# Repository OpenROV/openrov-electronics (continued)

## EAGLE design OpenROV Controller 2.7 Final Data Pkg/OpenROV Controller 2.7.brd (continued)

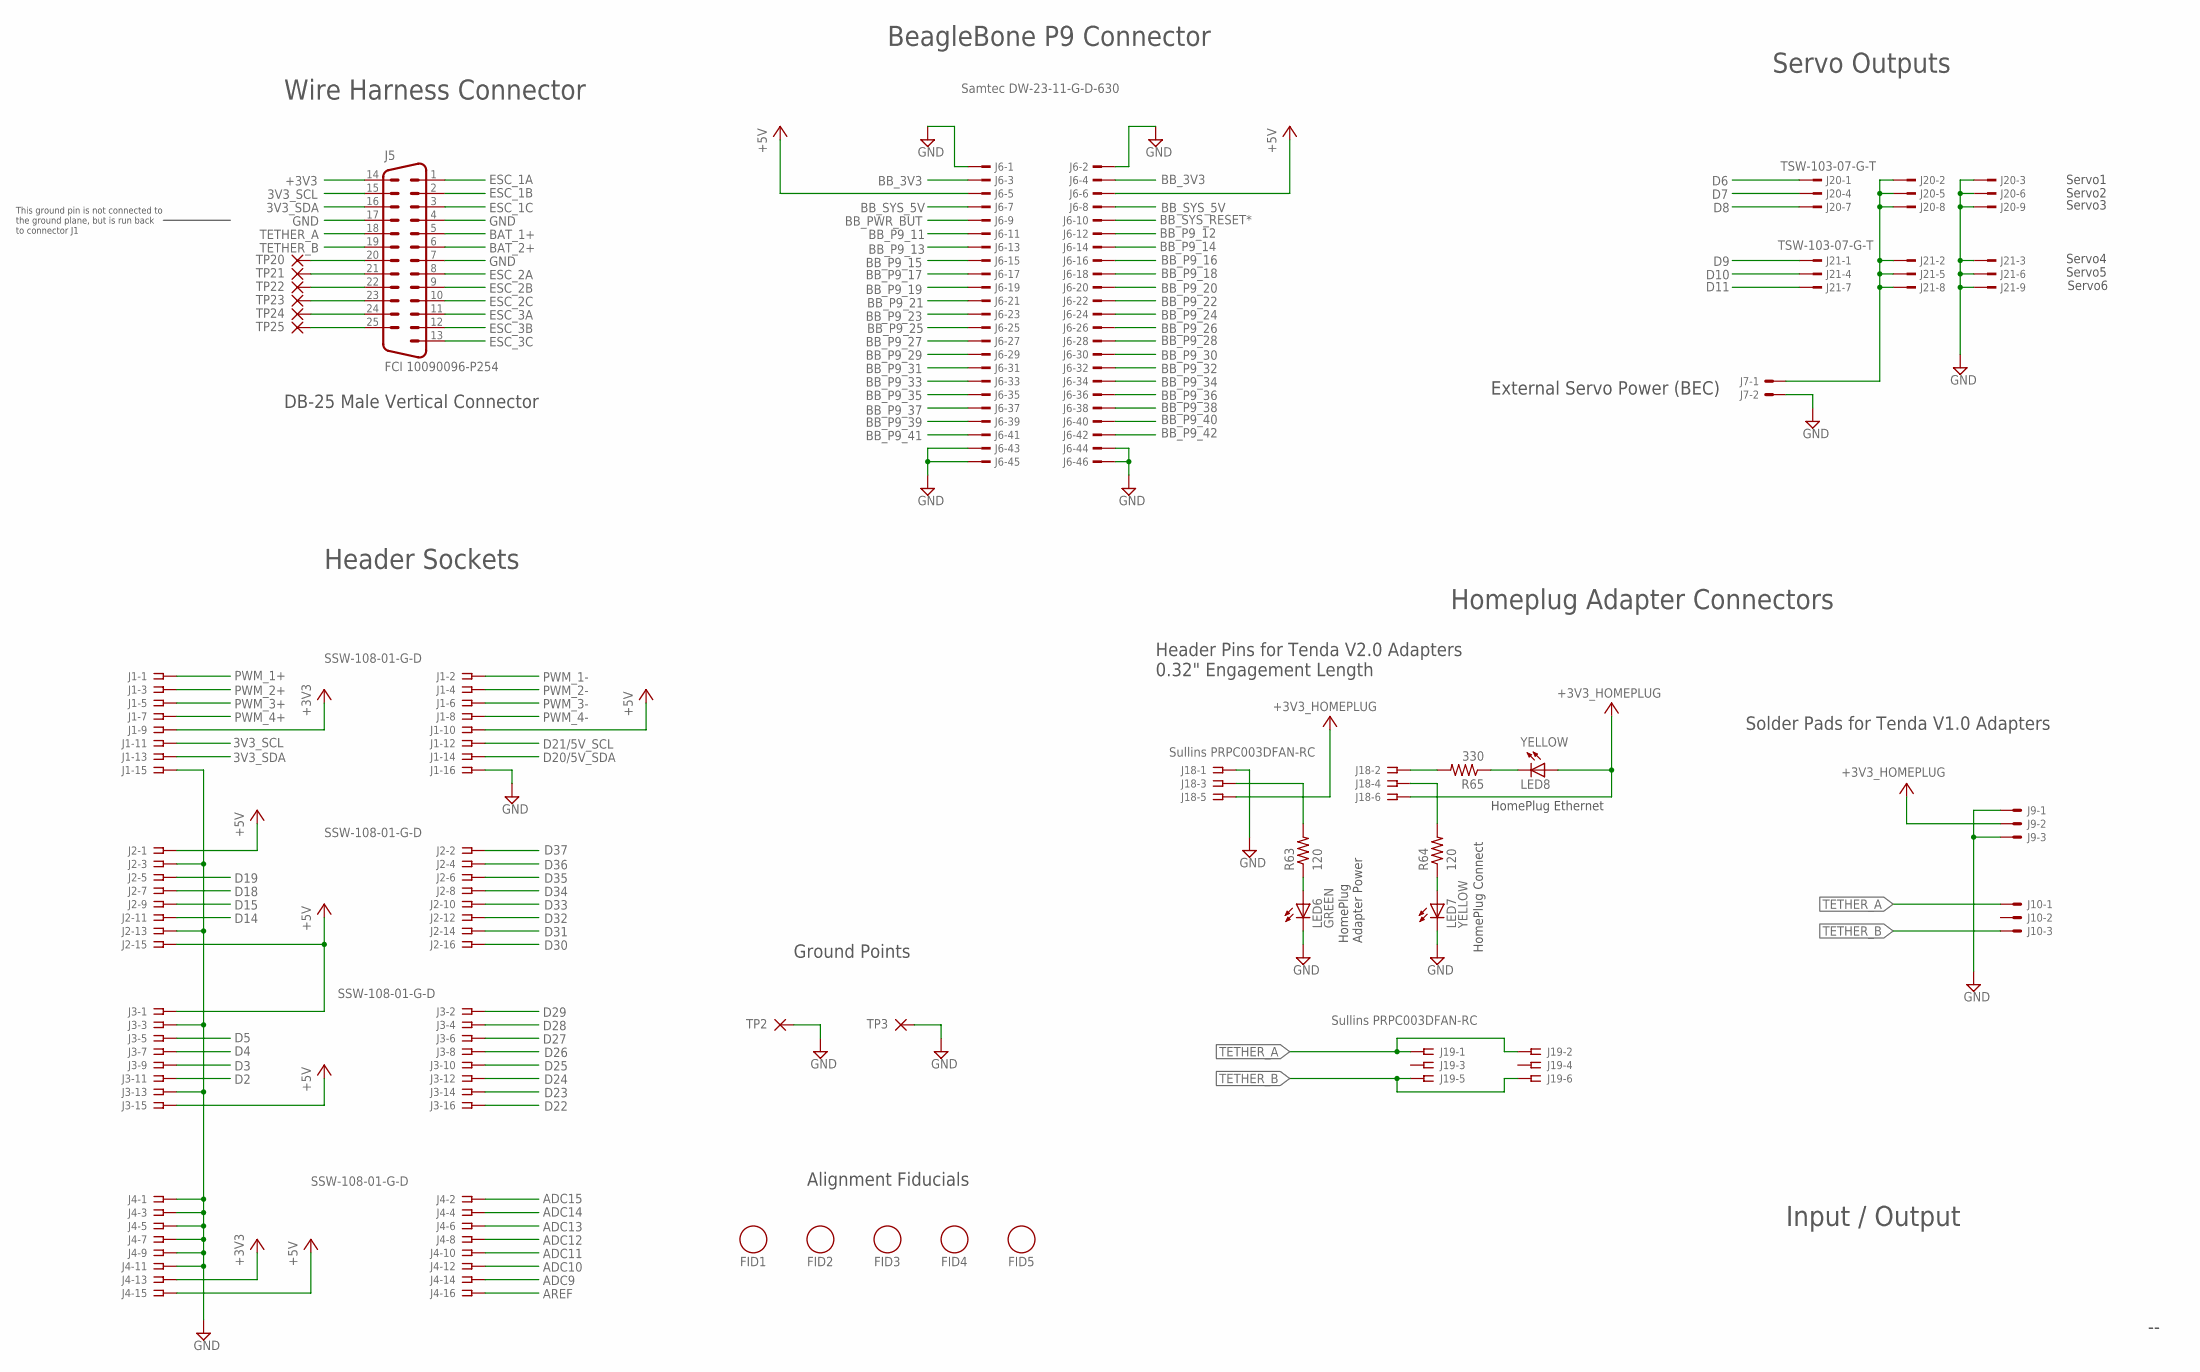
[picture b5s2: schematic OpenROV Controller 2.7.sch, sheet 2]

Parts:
FID1, FID2, FID3, FID4, FID5: FIDUCIAL_1
J1, J2, J3, J4: SSW-108-01-G-D; SSW-108-02-S-D
J5: FCI 10090096-P254; M25VP
J6: Samtec DW-23-11-G-D-630; TSW-123-02-S-D
J7: HDR_1X2X0.100-ALT_SILK; 22-23-2021_ALT_SILK
J9, J10: HDR_1X3X0.100-ALT_SILK; 22-23-2031_ALT_SILK
J18, J19: Sullins PRPC003DFAN-RC; SSW-103-02-S-D
J20, J21: TSW-103-07-G-T; HDR_PINS_3X3
LED6: GREEN; LED_CHIPLED_0603
LED7, LED8: YELLOW; LED_CHIPLED_0603
R63, R64: 120; R0603
R65: 330; R0603
TP2, TP3, TP20, TP21, TP22, TP23, TP24, TP25: TEST_PAD-1.0; 2.0/1.0

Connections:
3V3_SCL: J1.11, J5.15; also elsewhere on the board
3V3_SDA: J1.13, J5.16; also elsewhere on the board
+3V3: J1.9, J4.13, J5.14; also elsewhere on the board
+3V3_HOMEPLUG: J9.2, J18.5, J18.6, LED8.A; also elsewhere on the board
+5V: J1.10, J2.1, J2.15, J3.1, J3.15, J4.15, J6.5, J6.6; also elsewhere on the board
ADC9: J4.14; also elsewhere on the board
ADC10: J4.12; also elsewhere on the board
ADC11: J4.10; also elsewhere on the board
ADC12: J4.8; also elsewhere on the board
ADC13: J4.6; also elsewhere on the board
ADC14: J4.4; also elsewhere on the board
ADC15: J4.2; also elsewhere on the board
AREF: J4.16; also elsewhere on the board
BAT_1+: J5.5; also elsewhere on the board
BAT_2+: J5.6; also elsewhere on the board
BB_3V3: J6.3, J6.4; also elsewhere on the board
BB_P9_11: J6.11; also elsewhere on the board
BB_P9_12: J6.12
BB_P9_13: J6.13
BB_P9_14: J6.14
BB_P9_15: J6.15
BB_P9_16: J6.16
BB_P9_17: J6.17; also elsewhere on the board
BB_P9_18: J6.18; also elsewhere on the board
BB_P9_19: J6.19; also elsewhere on the board
BB_P9_20: J6.20; also elsewhere on the board
BB_P9_21: J6.21; also elsewhere on the board
BB_P9_22: J6.22; also elsewhere on the board
BB_P9_23: J6.23
BB_P9_24: J6.24; also elsewhere on the board
BB_P9_25: J6.25
BB_P9_26: J6.26; also elsewhere on the board
BB_P9_27: J6.27
BB_P9_28: J6.28
BB_P9_29: J6.29
BB_P9_30: J6.30
BB_P9_31: J6.31
BB_P9_32: J6.32
BB_P9_33: J6.33
BB_P9_34: J6.34
BB_P9_35: J6.35
BB_P9_36: J6.36
BB_P9_37: J6.37
BB_P9_38: J6.38
BB_P9_39: J6.39
BB_P9_40: J6.40
BB_P9_41: J6.41
BB_P9_42: J6.42
BB_PWR_BUT: J6.9
BB_SYS_5V: J6.7, J6.8
BB_SYS_RESET*: J6.10; also elsewhere on the board
D2: J3.11; also elsewhere on the board
D3: J3.9; also elsewhere on the board
D4: J3.7; also elsewhere on the board
D5: J3.5; also elsewhere on the board
D6: J20.P1; also elsewhere on the board
D7: J20.P4; also elsewhere on the board
D8: J20.P7; also elsewhere on the board
D9: J21.P1; also elsewhere on the board
D10: J21.P4; also elsewhere on the board
D11: J21.P7; also elsewhere on the board
D14: J2.11; also elsewhere on the board
D15: J2.9; also elsewhere on the board
D18: J2.7; also elsewhere on the board
D19: J2.5; also elsewhere on the board
D20/5V_SDA: J1.14; also elsewhere on the board
D21/5V_SCL: J1.12; also elsewhere on the board
D22: J3.16; also elsewhere on the board
D23: J3.14; also elsewhere on the board
D24: J3.12; also elsewhere on the board
D25: J3.10; also elsewhere on the board
D26: J3.8; also elsewhere on the board
D27: J3.6; also elsewhere on the board
D28: J3.4; also elsewhere on the board
D29: J3.2; also elsewhere on the board
D30: J2.16; also elsewhere on the board
D31: J2.14; also elsewhere on the board
D32: J2.12; also elsewhere on the board
D33: J2.10; also elsewhere on the board
D34: J2.8; also elsewhere on the board
D35: J2.6; also elsewhere on the board
D36: J2.4; also elsewhere on the board
D37: J2.2; also elsewhere on the board
ESC_1A: J5.1; also elsewhere on the board
ESC_1B: J5.2; also elsewhere on the board
ESC_1C: J5.3; also elsewhere on the board
ESC_2A: J5.8; also elsewhere on the board
ESC_2B: J5.9; also elsewhere on the board
ESC_2C: J5.10; also elsewhere on the board
ESC_3A: J5.11; also elsewhere on the board
ESC_3B: J5.12; also elsewhere on the board
ESC_3C: J5.13; also elsewhere on the board
GND: J1.15, J1.16, J2.3, J2.13, J3.3, J3.13, J4.1, J4.3, J4.5, J4.7, J4.9, J4.11, J5.4, J5.7, J5.17, J6.1, J6.2, J6.43, J6.44, J6.45, J6.46, J7.2, J9.1, J9.3, J18.1, J20.P3, J20.P6, J20.P9, J21.P3, J21.P6, J21.P9, LED6.C, LED7.C, TP2.1, TP3.1; also elsewhere on the board
unnamed: LED6.A, R63.1
unnamed: J5.24, TP24.1
unnamed: J5.20, TP20.1
unnamed: J7.1, J20.P2, J20.P5, J20.P8, J21.P2, J21.P5, J21.P8
unnamed: J5.21, TP21.1
unnamed: J5.22, TP22.1
unnamed: J5.23, TP23.1
unnamed: J5.25, TP25.1
unnamed: J18.3, R63.2
unnamed: J18.4, R64.2
unnamed: LED7.A, R64.1
unnamed: J18.2, R65.2
unnamed: LED8.C, R65.1
PWM_1+: J1.1; also elsewhere on the board
PWM_1-: J1.2; also elsewhere on the board
PWM_2+: J1.3; also elsewhere on the board
PWM_2-: J1.4; also elsewhere on the board
PWM_3+: J1.5; also elsewhere on the board
PWM_3-: J1.6; also elsewhere on the board
PWM_4+: J1.7; also elsewhere on the board
PWM_4-: J1.8; also elsewhere on the board
TETHER_A: J5.18, J10.1, J19.1, J19.2; also elsewhere on the board
TETHER_B: J5.19, J10.3, J19.5, J19.6; also elsewhere on the board

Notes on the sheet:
Input / Output
Servo Outputs
Wire Harness Connector
DB-25 Male Vertical Connector
Header Sockets
BeagleBone P9 Connector
Homeplug Adapter Connectors
Servo1
Servo2
Servo3
Servo4
Servo5
Servo6
External Servo Power (BEC)
This ground pin is not connected to the ground plane, but is run back to connector J1
Alignment Fiducials
Header Pins for Tenda V2.0 Adapters 0.32" Engagement Length
Solder Pads for Tenda V1.0 Adapters
Ground Points
HomePlug Ethernet
HomePlug Connect
HomePlug Adapter Power

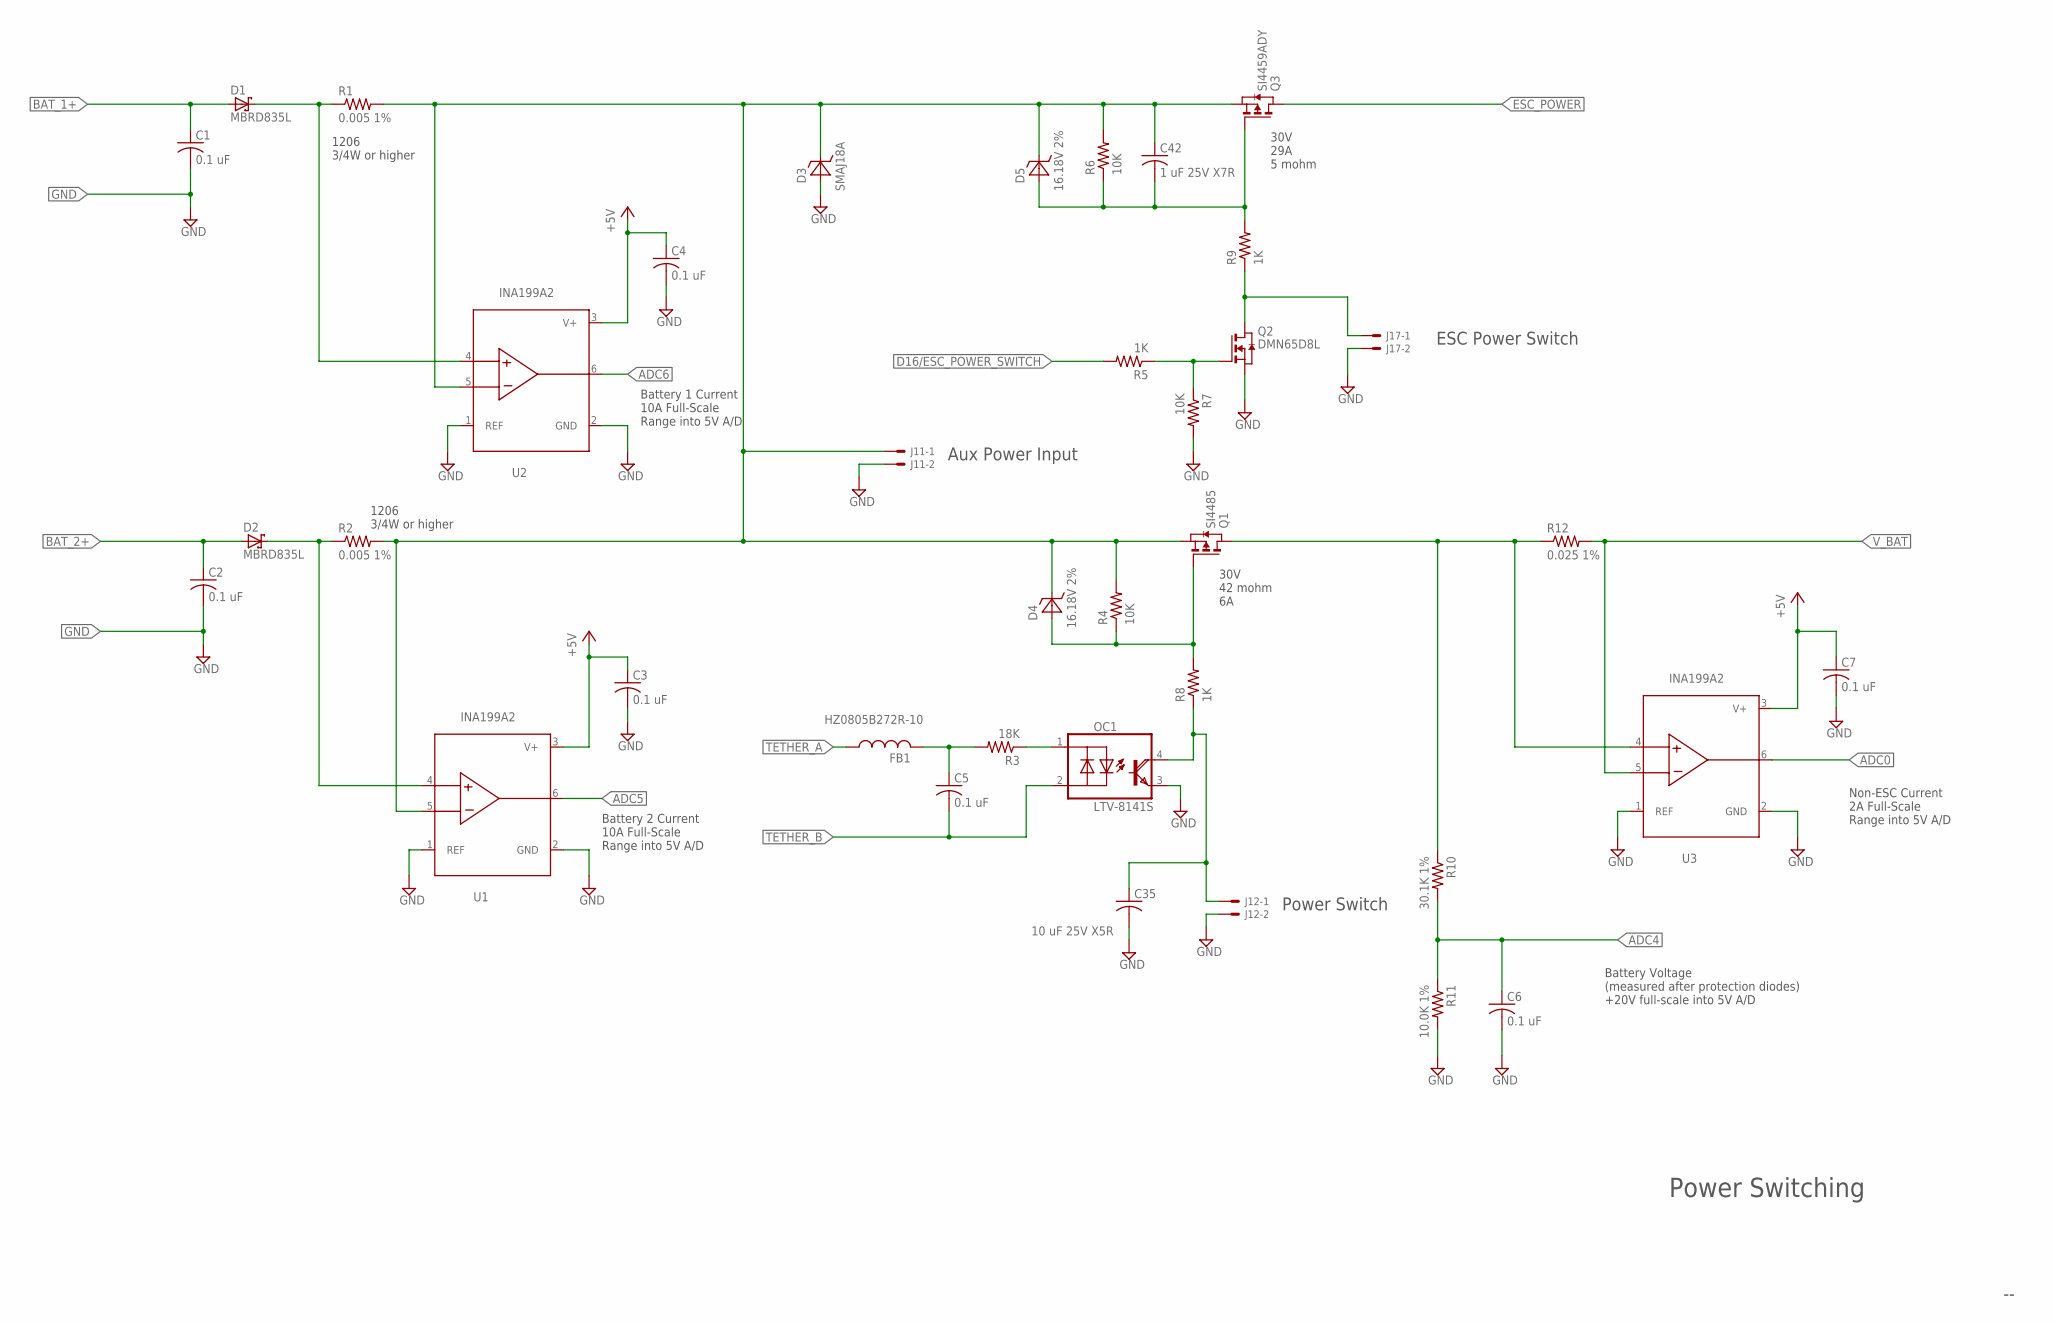
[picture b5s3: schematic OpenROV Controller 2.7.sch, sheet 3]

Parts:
C1, C2, C3, C4, C5, C6, C7: 0.1 uF; R0603
C35: 10 uF 25V X5R; R0805
C42: 1 uF 25V X7R; R0603
D1, D2: MBRD835L; DPAK
D3: SMAJ18A; DO214AC
D4, D5: 16.18V 2%; SOD323
FB1: HZ0805B272R-10; R0805
J11, J12, J17: HDR_1X2X0.100-ALT_SILK; 22-23-2021_ALT_SILK
OC1: LTV-8141S; DIL4-SMD
Q1: SI4485; SO8
Q2: DMN65D8L; SOT23
Q3: SI4459ADY; SO8
R1, R2: 0.005 1%; R1206
R3: 18K; R0603
R4, R6, R7: 10K; R0603
R5, R8, R9: 1K; R0603
R10: 30.1K 1%; R0603
R11: 10.0K 1%; R0603
R12: 0.025 1%; R0805
U1, U2, U3: INA199A2; SC70-6L

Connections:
+5V: C3.1, C4.1, C7.1, U1.3 (V+), U2.3 (V+), U3.3 (V+); also elsewhere on the board
ADC0: U3.6 (VOUT); also elsewhere on the board
ADC4: C6.1, R10.2, R11.1; also elsewhere on the board
ADC5: U1.6 (VOUT); also elsewhere on the board
ADC6: U2.6 (VOUT); also elsewhere on the board
BAT_1+: C1.1, D1.1 (A), D1.3 (A); also elsewhere on the board
BAT_1-1: Q1.5 (D), Q1.6 (D), Q1.7 (D), Q1.8 (D), R10.1, R12.1, U3.4 (IN+)
BAT_2+: C2.1, D2.1 (A), D2.3 (A); also elsewhere on the board
D16/ESC_POWER_SWITCH: R5.2; also elsewhere on the board
ESC_POWER: Q3.5 (D), Q3.6 (D), Q3.7 (D), Q3.8 (D); also elsewhere on the board
GND: C1.2, C2.2, C3.2, C4.2, C6.2, C7.2, C35.2, D3.A, J11.2, J12.2, J17.2, OC1.3 (E), Q2.2 (S), R7.2, R11.2, U1.1 (REF), U1.2 (GND), U2.1 (REF), U2.2 (GND), U3.1 (REF), U3.2 (GND); also elsewhere on the board
unnamed: OC1.1 (IN-A), R3.1
unnamed: C42.2, D5.A, Q3.4 (G), R6.1, R9.2
unnamed: J17.1, Q2.3 (D), R9.1
unnamed: D1.4 (C), R1.1, U2.4 (IN+)
unnamed: Q2.1 (G), R5.1, R7.1
unnamed: C42.1, D3.C, D4.C, D5.C, J11.1, Q1.1 (S), Q1.2 (S), Q1.3 (S), Q3.1 (S), Q3.2 (S), Q3.3 (S), R1.2, R2.2, R4.2, R6.2, U1.5 (IN-), U2.5 (IN-)
unnamed: D4.A, Q1.4 (G), R4.1, R8.2
unnamed: C5.1, FB1.2, R3.2
unnamed: D2.4 (C), R2.1, U1.4 (IN+)
unnamed: C35.1, J12.1, OC1.4 (C), R8.1
TETHER_A: FB1.1; also elsewhere on the board
TETHER_B: C5.2, OC1.2 (IN-B); also elsewhere on the board
V_BAT: R12.2, U3.5 (IN-); also elsewhere on the board

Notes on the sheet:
Power Switching
30V 42 mohm 6A
30V 29A 5 mohm
1206 3/4W or higher
Battery 1 Current 10A Full-Scale Range into 5V A/D
Battery 2 Current 10A Full-Scale Range into 5V A/D
Non-ESC Current 2A Full-Scale Range into 5V A/D
Power Switch
Aux Power Input
Battery Voltage (measured after protection diodes) +20V full-scale into 5V A/D
ESC Power Switch

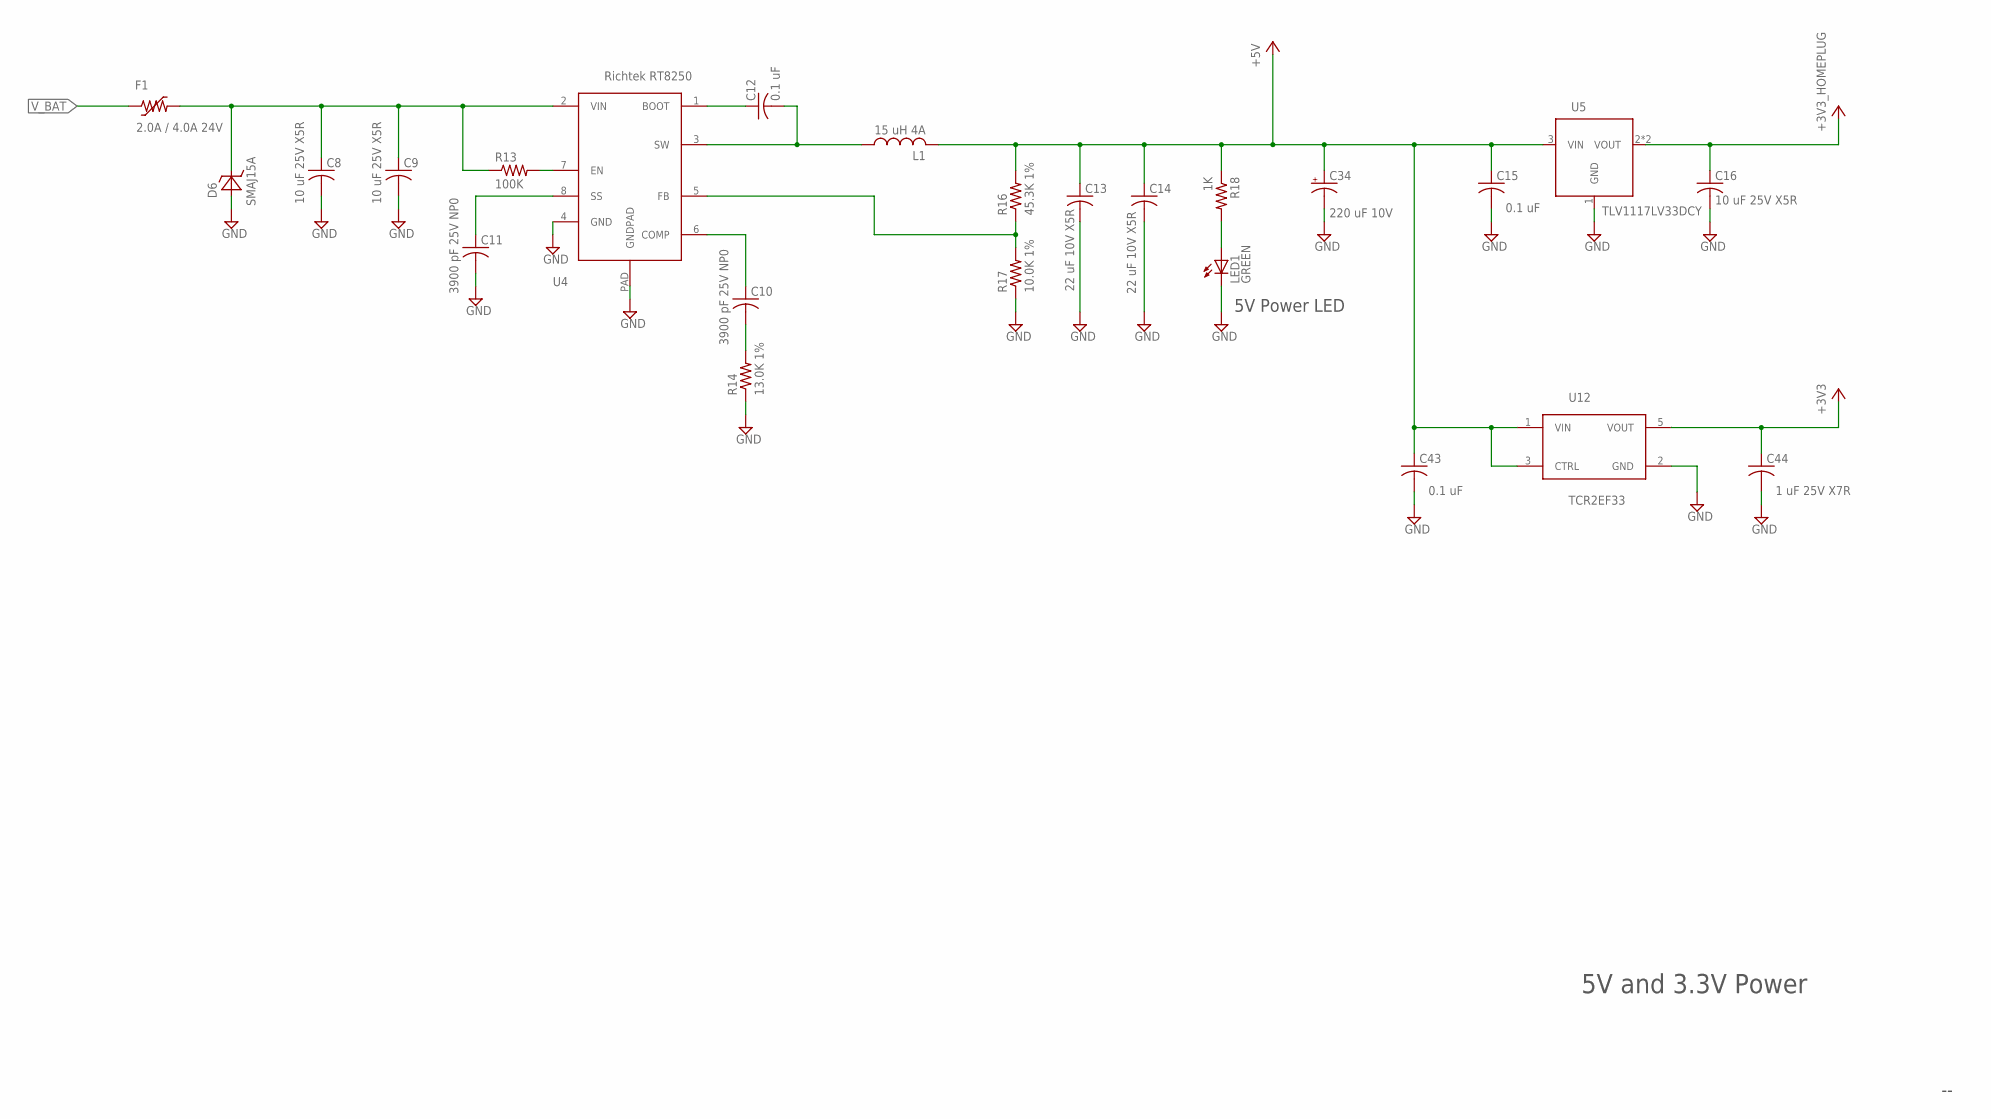
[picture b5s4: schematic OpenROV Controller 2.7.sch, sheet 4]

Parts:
C8, C9, C16: 10 uF 25V X5R; R0805
C10, C11: 3900 pF 25V NP0; R0603
C12, C15, C43: 0.1 uF; R0603
C13, C14: 22 uF 10V X5R; R0805
C34: 220 uF 10V; NICHICON_8MM
C44: 1 uF 25V X7R; R0603
D6: SMAJ15A; DO214AC
F1: 2.0A / 4.0A 24V; R2920
L1: 15 uH 4A; INDUCTOR_BOURNS_12X0
LED1: GREEN; LED_CHIPLED_0603
R13: 100K; R0603
R14: 13.0K 1%; R0603
R16: 45.3K 1%; R0603
R17: 10.0K 1%; R0603
R18: 1K; R0603
U4: Richtek RT8250; SO8-THERMAL
U5: TLV1117LV33DCY; SOT223
U12: TCR2EF33; SOT23-5L

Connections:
+3V3: C44.1, U12.5 (VOUT); also elsewhere on the board
+3V3_HOMEPLUG: C16.1, U5.2 (VOUT), U5.4 (VOUT); also elsewhere on the board
+5V: C13.1, C14.1, C15.1, C34.+, C43.1, L1.2, R16.2, R18.1, U5.3 (VIN), U12.1 (VIN), U12.3 (CTRL); also elsewhere on the board
FUSED_VBAT: C8.1, C9.1, D6.C, F1.2, R13.1, U4.2 (VIN)
GND: C8.2, C9.2, C11.2, C13.2, C14.2, C15.2, C16.2, C34.-, C43.2, C44.2, D6.A, LED1.C, R14.1, R17.1, U4.4 (GND), U4.PAD (GNDPAD), U5.1 (GND), U12.2 (GND); also elsewhere on the board
unnamed: LED1.A, R18.2
unnamed: R16.1, R17.2, U4.5 (FB)
unnamed: R13.2, U4.7 (EN)
unnamed: C11.1, U4.8 (SS)
unnamed: C12.1, U4.1 (BOOT)
unnamed: C12.2, L1.1, U4.3 (SW)
unnamed: C10.1, U4.6 (COMP)
unnamed: C10.2, R14.2
V_BAT: F1.1; also elsewhere on the board

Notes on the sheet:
5V and 3.3V Power
5V Power LED

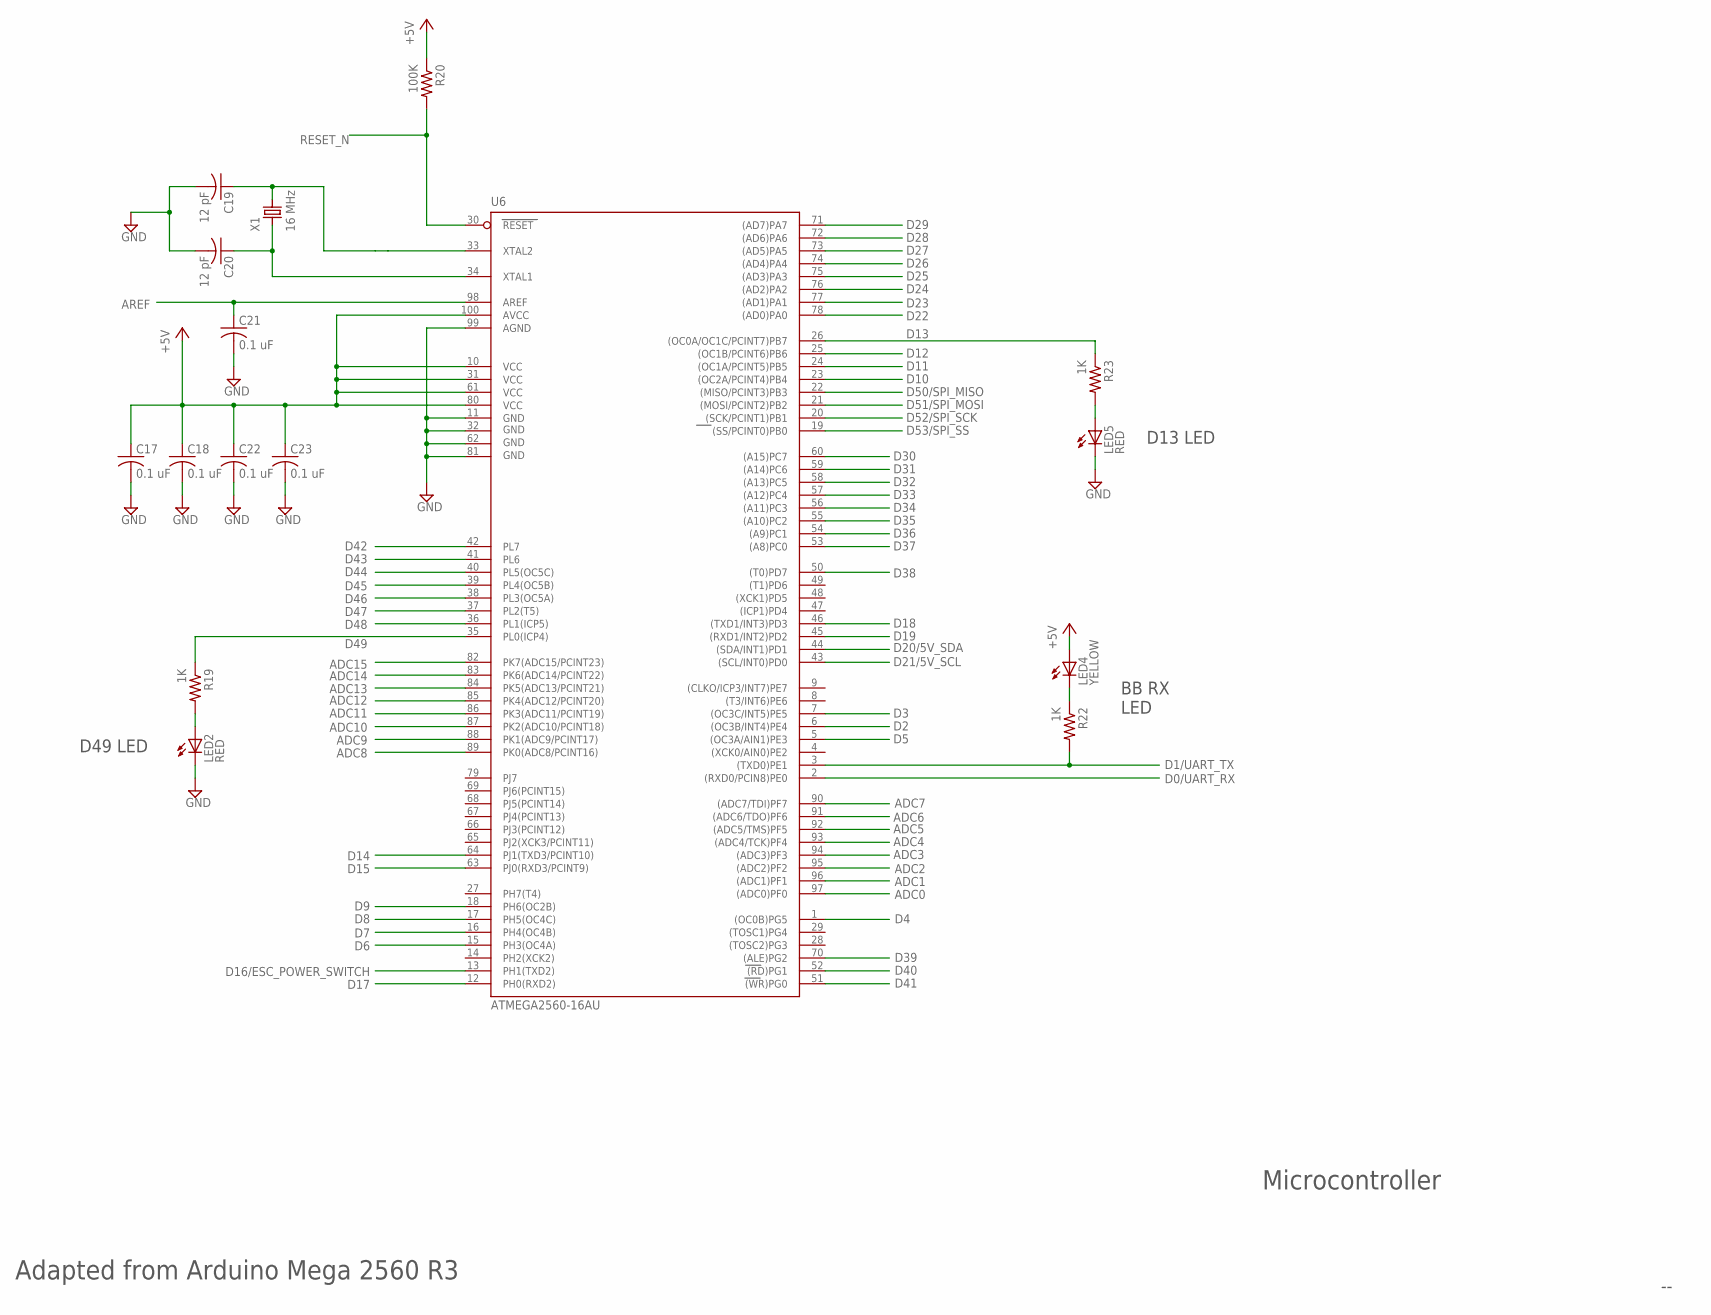
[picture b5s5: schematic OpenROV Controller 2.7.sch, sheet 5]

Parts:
C17, C18, C21, C22, C23: 0.1 uF; R0603
C19, C20: 12 pF; R0603
LED2, LED5: RED; LED_CHIPLED_0603
LED4: YELLOW; LED_CHIPLED_0603
R19, R22, R23: 1K; R0603
R20: 100K; R0603
U6: ATMEGA2560-16AU; SMARTPRJ_TQFP100
X1: 16 MHz; DISCRETE_2P-SMD-5X3.2

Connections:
+5V: C17.1, C18.1, C22.1, C23.1, LED4.A, R20.1, U6.10 (VCC), U6.31 (VCC1), U6.61 (VCC2), U6.80 (VCC3), U6.100 (AVCC); also elsewhere on the board
ADC0: U6.97 ((ADC0)PF0); also elsewhere on the board
ADC1: U6.96 ((ADC1)PF1); also elsewhere on the board
ADC2: U6.95 ((ADC2)PF2); also elsewhere on the board
ADC3: U6.94 ((ADC3)PF3); also elsewhere on the board
ADC4: U6.93 ((ADC4/TCK)PF4); also elsewhere on the board
ADC5: U6.92 ((ADC5/TMS)PF5); also elsewhere on the board
ADC6: U6.91 ((ADC6/TDO)PF6); also elsewhere on the board
ADC7: U6.90 ((ADC7/TDI)PF7); also elsewhere on the board
ADC8: U6.89 (PK0(ADC8/PCINT16)); also elsewhere on the board
ADC9: U6.88 (PK1(ADC9/PCINT17)); also elsewhere on the board
ADC10: U6.87 (PK2(ADC10/PCINT18)); also elsewhere on the board
ADC11: U6.86 (PK3(ADC11/PCINT19)); also elsewhere on the board
ADC12: U6.85 (PK4(ADC12/PCINT20)); also elsewhere on the board
ADC13: U6.84 (PK5(ADC13/PCINT21)); also elsewhere on the board
ADC14: U6.83 (PK6(ADC14/PCINT22)); also elsewhere on the board
ADC15: U6.82 (PK7(ADC15/PCINT23)); also elsewhere on the board
AREF: C21.1, U6.98 (AREF); also elsewhere on the board
D0/UART_RX: U6.2 ((RXD0/PCIN8)PE0); also elsewhere on the board
D1/UART_TX: R22.2, U6.3 ((TXD0)PE1); also elsewhere on the board
D2: U6.6 ((OC3B/INT4)PE4); also elsewhere on the board
D3: U6.7 ((OC3C/INT5)PE5); also elsewhere on the board
D4: U6.1 ((OC0B)PG5); also elsewhere on the board
D5: U6.5 ((OC3A/AIN1)PE3); also elsewhere on the board
D6: U6.15 (PH3(OC4A)); also elsewhere on the board
D7: U6.16 (PH4(OC4B)); also elsewhere on the board
D8: U6.17 (PH5(OC4C)); also elsewhere on the board
D9: U6.18 (PH6(OC2B)); also elsewhere on the board
D10: U6.23 ((OC2A/PCINT4)PB4); also elsewhere on the board
D11: U6.24 ((OC1A/PCINT5)PB5); also elsewhere on the board
D12: U6.25 ((OC1B/PCINT6)PB6); also elsewhere on the board
D13: R23.1, U6.26 ((OC0A/OC1C/PCINT7)PB7)
D14: U6.64 (PJ1(TXD3/PCINT10)); also elsewhere on the board
D15: U6.63 (PJ0(RXD3/PCINT9)); also elsewhere on the board
D16/ESC_POWER_SWITCH: U6.13 (PH1(TXD2)); also elsewhere on the board
D17: U6.12 (PH0(RXD2))
D18: U6.46 ((TXD1/INT3)PD3); also elsewhere on the board
D19: U6.45 ((RXD1/INT2)PD2); also elsewhere on the board
D20/5V_SDA: U6.44 ((SDA/INT1)PD1); also elsewhere on the board
D21/5V_SCL: U6.43 ((SCL/INT0)PD0); also elsewhere on the board
D22: U6.78 ((AD0)PA0); also elsewhere on the board
D23: U6.77 ((AD1)PA1); also elsewhere on the board
D24: U6.76 ((AD2)PA2); also elsewhere on the board
D25: U6.75 ((AD3)PA3); also elsewhere on the board
D26: U6.74 ((AD4)PA4); also elsewhere on the board
D27: U6.73 ((AD5)PA5); also elsewhere on the board
D28: U6.72 ((AD6)PA6); also elsewhere on the board
D29: U6.71 ((AD7)PA7); also elsewhere on the board
D30: U6.60 ((A15)PC7); also elsewhere on the board
D31: U6.59 ((A14)PC6); also elsewhere on the board
D32: U6.58 ((A13)PC5); also elsewhere on the board
D33: U6.57 ((A12)PC4); also elsewhere on the board
D34: U6.56 ((A11)PC3); also elsewhere on the board
D35: U6.55 ((A10)PC2); also elsewhere on the board
D36: U6.54 ((A9)PC1); also elsewhere on the board
D37: U6.53 ((A8)PC0); also elsewhere on the board
D38: U6.50 ((T0)PD7)
D39: U6.70 ((ALE)PG2)
D40: U6.52 ((RD)PG1)
D41: U6.51 ((WR)PG0)
D42: U6.42 (PL7)
D43: U6.41 (PL6)
D44: U6.40 (PL5(OC5C)); also elsewhere on the board
D45: U6.39 (PL4(OC5B)); also elsewhere on the board
D46: U6.38 (PL3(OC5A)); also elsewhere on the board
D47: U6.37 (PL2(T5))
D48: U6.36 (PL1(ICP5))
D49: R19.1, U6.35 (PL0(ICP4))
D50/SPI_MISO: U6.22 ((MISO/PCINT3)PB3); also elsewhere on the board
D51/SPI_MOSI: U6.21 ((MOSI/PCINT2)PB2); also elsewhere on the board
D52/SPI_SCK: U6.20 ((SCK/PCINT1)PB1); also elsewhere on the board
D53/SPI_SS: U6.19 ((SS/PCINT0)PB0); also elsewhere on the board
GND: C17.2, C18.2, C19.2, C20.2, C21.2, C22.2, C23.2, LED2.C, LED5.C, U6.11 (GND), U6.32 (GND1), U6.62 (GND2), U6.81 (GND3), U6.99 (AGND); also elsewhere on the board
unnamed: LED2.A, R19.2
unnamed: C19.1, U6.33 (XTAL2), X1.2
unnamed: C20.1, U6.34 (XTAL1), X1.1
unnamed: LED5.A, R23.2
unnamed: LED4.C, R22.1
RESET_N: R20.2, U6.30 (RESET); also elsewhere on the board

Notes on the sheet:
Microcontroller
Adapted from Arduino Mega 2560 R3
D13 LED
D49 LED
BB RX LED

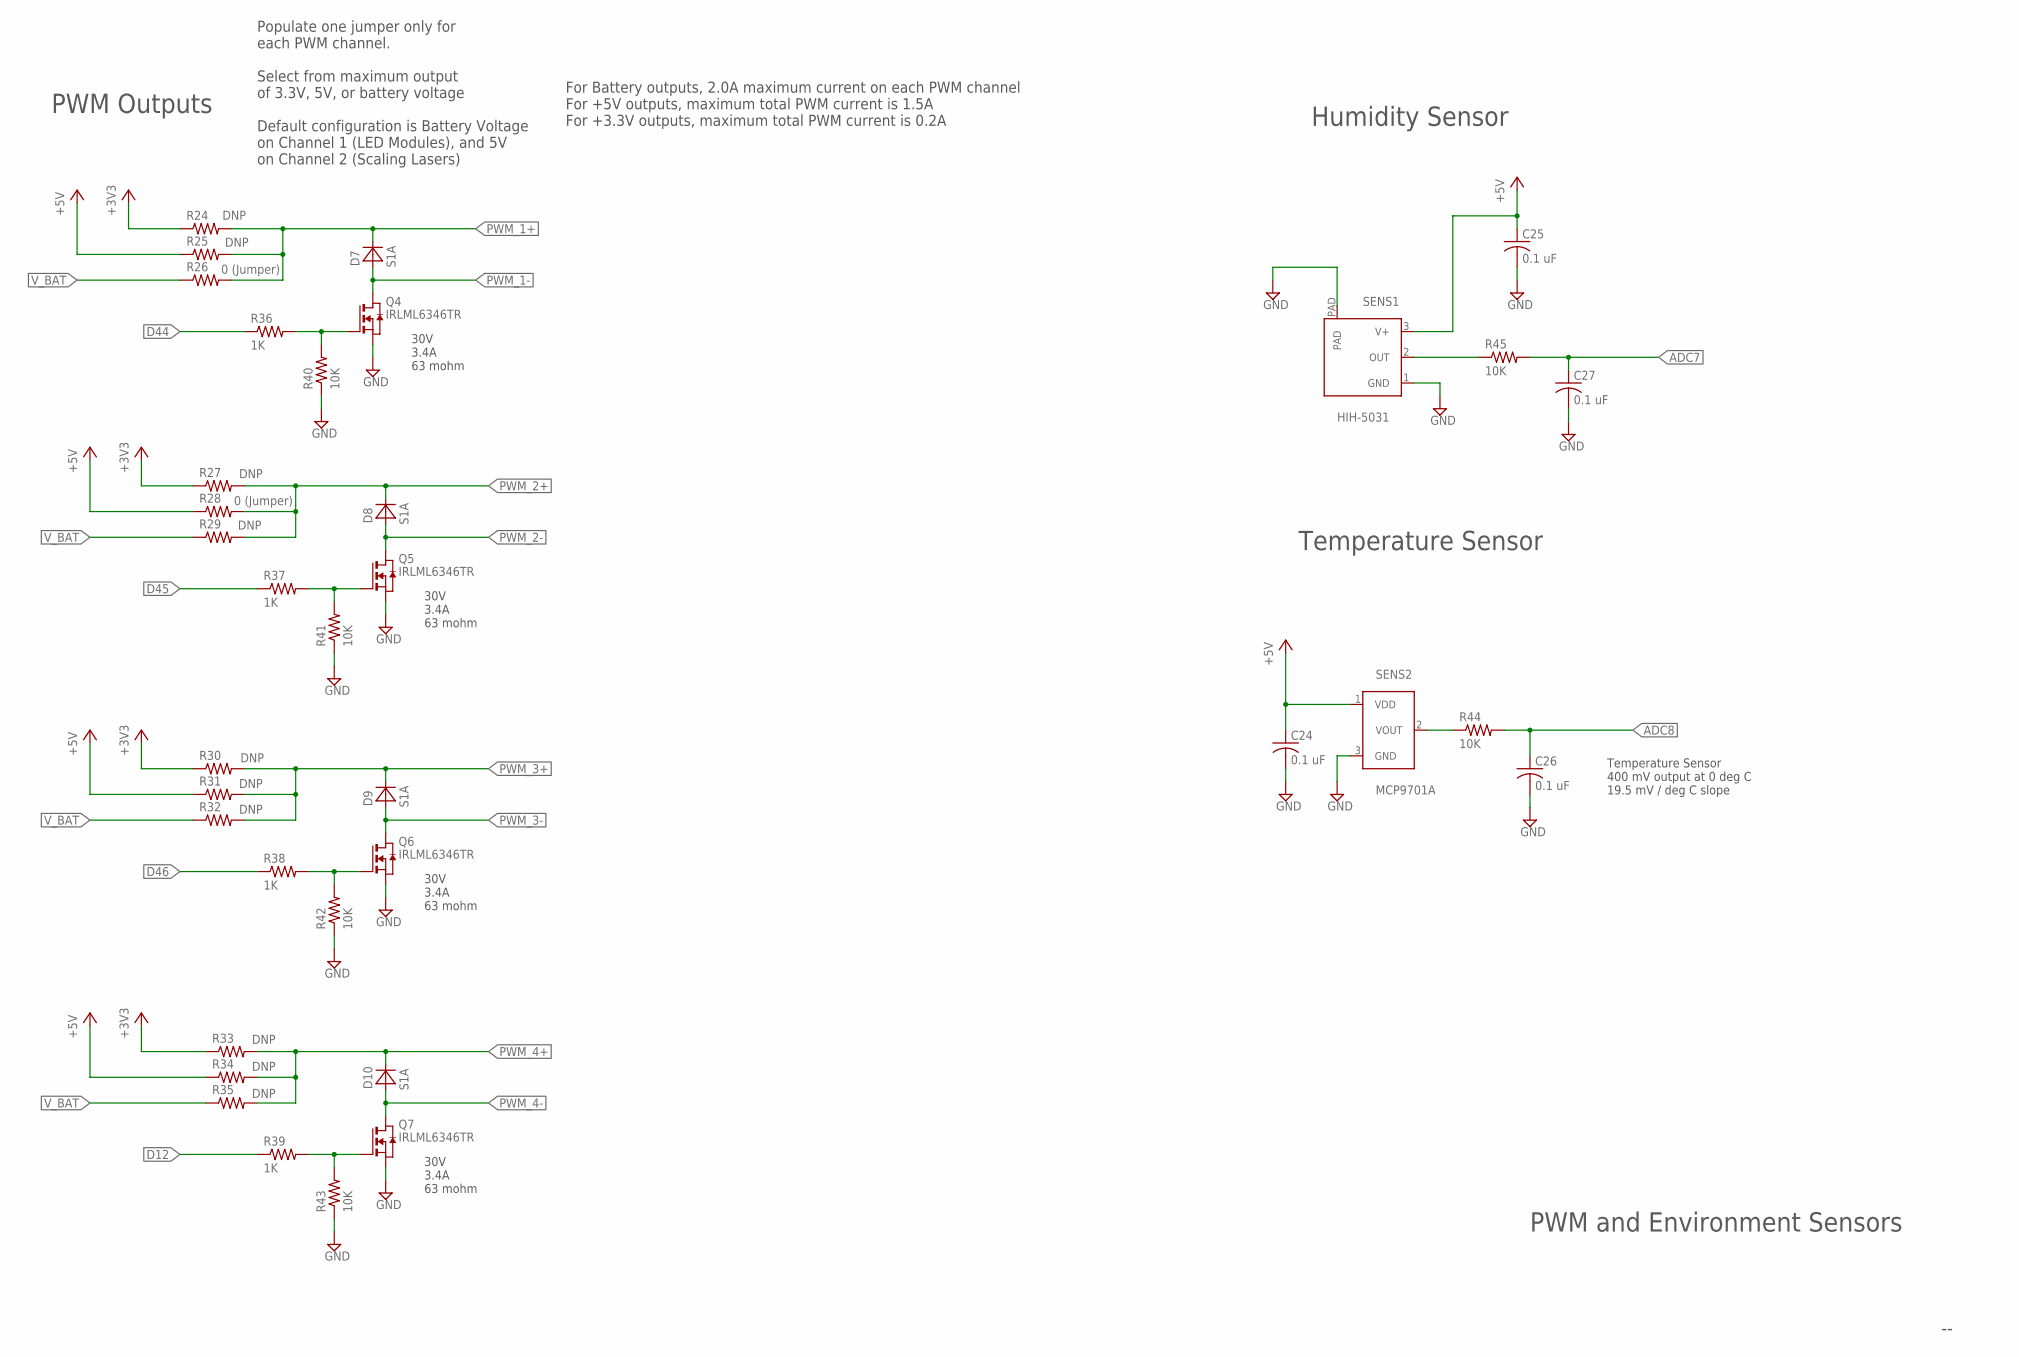
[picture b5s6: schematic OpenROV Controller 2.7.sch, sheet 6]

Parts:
C24, C25, C26, C27: 0.1 uF; R0603
D7, D8, D9, D10: S1A; DO214AC
Q4, Q5, Q6, Q7: IRLML6346TR; SOT23
R24, R25, R27, R29, R30, R31, R32, R33, R34, R35: DNP; R0805
R26, R28: 0 (Jumper); R0805
R36, R37, R38, R39: 1K; R0603
R40, R41, R42, R43, R44, R45: 10K; R0603
SENS1: HIH-5031
SENS2: MCP9701A; SOT23

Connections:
+3V3: R24.1, R27.1, R30.1, R33.1; also elsewhere on the board
+5V: C24.1, C25.1, R25.1, R28.1, R31.1, R34.1, SENS1.3 (V+), SENS2.1 (VDD); also elsewhere on the board
ADC7: C27.1, R45.2; also elsewhere on the board
ADC8: C26.1, R44.2; also elsewhere on the board
D12: R39.1; also elsewhere on the board
D44: R36.1; also elsewhere on the board
D45: R37.1; also elsewhere on the board
D46: R38.1; also elsewhere on the board
GND: C24.2, C25.2, C26.2, C27.2, Q4.2 (S), Q5.2 (S), Q6.2 (S), Q7.2 (S), R40.1, R41.1, R42.1, R43.1, SENS1.1 (GND), SENS1.PAD, SENS2.3 (GND); also elsewhere on the board
unnamed: R45.1, SENS1.2 (OUT)
unnamed: R44.1, SENS2.2 (VOUT)
unnamed: Q4.1 (G), R36.2, R40.2
unnamed: Q5.1 (G), R37.2, R41.2
unnamed: Q6.1 (G), R38.2, R42.2
unnamed: Q7.1 (G), R39.2, R43.2
PWM_1+: D7.C, R24.2, R25.2, R26.2; also elsewhere on the board
PWM_1-: D7.A, Q4.3 (D); also elsewhere on the board
PWM_2+: D8.C, R27.2, R28.2, R29.2; also elsewhere on the board
PWM_2-: D8.A, Q5.3 (D); also elsewhere on the board
PWM_3+: D9.C, R30.2, R31.2, R32.2; also elsewhere on the board
PWM_3-: D9.A, Q6.3 (D); also elsewhere on the board
PWM_4+: D10.C, R33.2, R34.2, R35.2; also elsewhere on the board
PWM_4-: D10.A, Q7.3 (D); also elsewhere on the board
V_BAT: R26.1, R29.1, R32.1, R35.1; also elsewhere on the board

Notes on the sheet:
PWM and Environment Sensors
30V 3.4A 63 mohm
PWM Outputs
Humidity Sensor
Temperature Sensor
Temperature Sensor 400 mV output at 0 deg C 19.5 mV / deg C slope
Populate one jumper only for each PWM channel. Select from maximum output of 3.3V, 5V, or battery voltage Default configuration is Battery Voltage on Channel 1 (LED Modules), and 5V on Channel 2 (Scaling Lasers)
For Battery outputs, 2.0A maximum current on each PWM channel For +5V outputs, maximum total PWM current is 1.5A For +3.3V outputs, maximum total PWM current is 0.2A
